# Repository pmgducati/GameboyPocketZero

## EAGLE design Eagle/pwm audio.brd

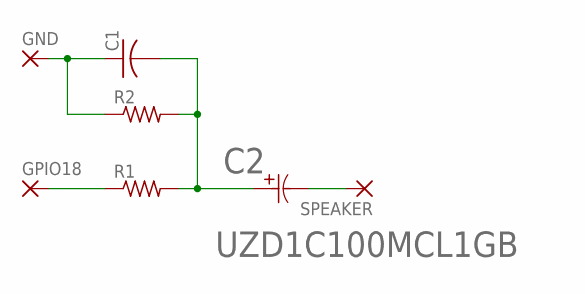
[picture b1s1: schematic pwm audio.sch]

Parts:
C1: C-USC1206; C1206
C2: UZD1C100MCL1GB; PCAP_5X3-ELECT
GND: 2,54/1,0
GPIO18: 2,54/1,0
R1, R2: R-US_R1206; R1206
SPEAKER: 2,54/1,0

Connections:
GND: C1.1, GND.1, R2.1
unnamed: C1.2, C2.1 (11), R1.2, R2.2
unnamed: GPIO18.1, R1.1
unnamed: C2.2 (22), SPEAKER.1

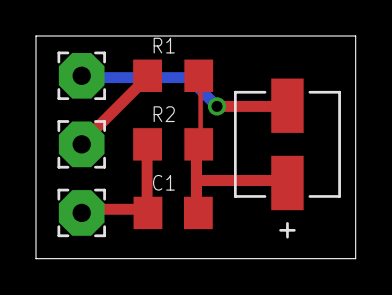
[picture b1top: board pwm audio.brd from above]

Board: 2 copper layers, 17.8 x 12.4 mm, 7 parts (0 on the bottom side), 4 nets.

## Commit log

2016-10-20 Adding PWM Audio Baord and Bezel CAD

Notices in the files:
parts and their libraries:
COPYRIGHT: Copyright (C) 2015 Accelerated Designs. All rights reserved
